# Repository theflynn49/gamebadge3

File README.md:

<b>New 2024 march 2</b> : Good news : all screens work, including the 7-pins ones ! 
Read the details in ST7789_280x240/TFT_adapt/README.md

This a a fork of BenHeck's GameBadge3 repo

I have a branch here "ST7789_280x240" where I made some changes
to support wider screens

There is also a TZT_adapt directory with gerber files for an adapter for cheap AliExpress screens (ST7789V screens with a connector layout like (Gnd/Vcc/Scl/Sda/Res/DC/CS/Blk)

To use it, modify code/Arduino libraries/pico_ST7789/pico_ST7789.cpp to set the width of your physical screen, i.e. 320, 280 or 240.
You should set also the appropriate rotation, leaving it to "1" if possible by rotating physically the screen (soldering it
in the left or right slot of the TZT adpter) 

If you do that, NOT-recompiled games may work on your screen without modifications,

exemple :
  #define SCR_WIDTH 320
  #define LCD_ROTATION 1

and then you should recompile.

Centering vertically has not been done yet, and will probably never be.

Don't forget to do all this on the correct branch :

<code>
git clone https://github.com/theflynn49/gamebadge3.git
git checkout ST7789_280x240
</code>

Warning : Games for GB3 must be compiled with 
  - flash size=1MB / Sketch Size=1MB
  - CPU Speed = 125Mhz (important !)
  - USB Stack : Adafruit TinyUSB

Have fun.
jF

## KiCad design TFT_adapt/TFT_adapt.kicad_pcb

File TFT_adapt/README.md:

This is a kicad project for an adapter board to install a cheap Aliexpress TZT screen on your GameBadge.

Beware : BenHeck is NOT recommanding this, since cheap display modules may not work well.

On another hand, they cost about $3 instead of $17 as of today.

I tried these up to now :
 
 - <url>https://fr.aliexpress.com/item/1005005921876295.html</url> (round corners without pixels, upside-down)
 - <url>https://fr.aliexpress.com/item/1005005933513340.html</url> (tested OK, is upside-down)
 - <url>https://fr.aliexpress.com/item/32858069771.html</url> (7-wires, tested OK, is upside down)

For the 7-bit screen, you need to change gameBadgePico.cpp, and make the following change :
<code>
const struct st7789_config lcd_config = {
    .spi      = PICO_DEFAULT_SPI_INSTANCE,
    .gpio_din = PICO_DEFAULT_SPI_TX_PIN,
    .gpio_clk = PICO_DEFAULT_SPI_SCK_PIN,
    .gpio_cs  = PICO_DEFAULT_SPI_CSN_PIN,
    .gpio_dc  = 20,
    .gpio_rst = 21,
    .gpio_bl  = 22
};
</code>

has to be replaced by :
<code>
const struct st7789_config lcd_config = {
    .spi      = PICO_DEFAULT_SPI_INSTANCE,
    .gpio_din = PICO_DEFAULT_SPI_TX_PIN,
    .gpio_clk = PICO_DEFAULT_SPI_SCK_PIN,
    .gpio_cs  = -1, // <- to indicate only 7 pins, no CS
    .gpio_dc  = 20,
    .gpio_rst = 21,
    .gpio_bl  =  PICO_DEFAULT_SPI_CSN_PIN // <- if you use my TFT_adapt board this will be misrouted, so use CS instead of BLK
};
</code>
and you'll leave the pin "Blk" not connected on all connectors.
<br/>
Important note : make sure you use my version of gameBadgePico.cpp (as of 2024/02/24), which contains a modification to make the chinese TZT screen stable.
I pushed this mod on both my branches of this repo.

I tested the gerber files with PCBway.

This has been tested now, it works fine. 

Have fun.

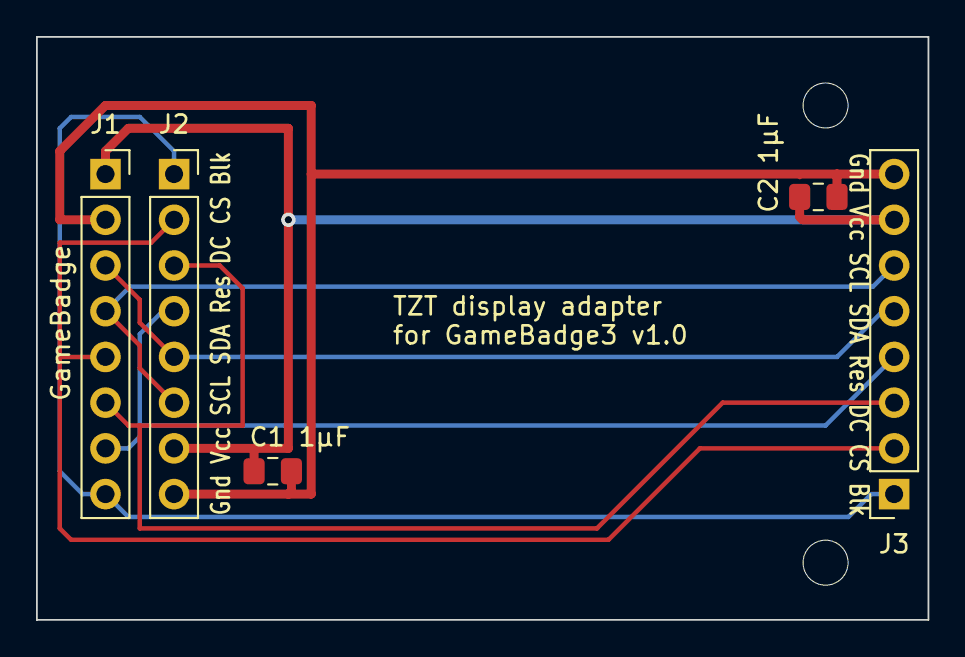
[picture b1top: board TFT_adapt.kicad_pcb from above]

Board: 2 copper layers, 49.5 x 32.4 mm, 7 parts (0 on the bottom side), 8 nets.

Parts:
C1 1µF, C2 1µF: 1µF; C_0805_2012Metric_Pad1.18x1.45mm_HandSolder
H1, H2: MountingHole; MountingHole_2.5mm
J1, J2, J3: Conn_01x08; PinSocket_1x08_P2.54mm_Vertical

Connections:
unnamed: C1 1µF.1, C2 1µF.1, J1.1, J2.7, J3.7
unnamed: C1 1µF.2, C2 1µF.2, J1.2, J2.8, J3.8
unnamed: J1.3, J2.5, J3.5
unnamed: J1.4, J2.6, J3.6
unnamed: J1.5, J2.2, J3.2
unnamed: J1.6, J2.3, J3.3
unnamed: J1.7, J2.4, J3.4
unnamed: J1.8, J2.1, J3.1

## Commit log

2024-02-09 add support for 320x240 and/or 280x240 screens; clean up a bit the screen size params
2024-02-09 add README.md
2024-02-14 Add kicad files for a screen adapter board to fit cheap asian screens
2024-02-22 Update README.md
    update list of screens
2024-02-24 Improve screen stability by insuring there is a 1µs delay after a dma transfer is done before starting a new one. This modification insure that there is no collision with a previous block, so the pre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
    A few other modifications have been made removing some constants and uselesss calls.
2024-02-24 Update README.md
    update status of the cheap TZT screens
2024-02-25 Before starting a new DMA cycle, we need to wait that the previous DMA is finished AND that the SPI is empty !
2024-02-25 Clean code, remove unneeded state
2024-02-28 The screen shift was not working for Rotation==1; this is fixed now, and I cleaned up that code a bit.
2024-02-28 add image to README.md
2024-02-28 Add picture to README.md
2024-03-02 7-pins screens work !
    7-pins screens work !
2024-03-02 all screens work
    Update README.md
